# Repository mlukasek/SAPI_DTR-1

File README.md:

# SAPI-1 DTR-1 (Deska Testeru a RAM)

DTR-1 je modení deska pro starší 8-bitový počítač SAPI-1. Jedná se o poměrně univerzální desku, která může sloužit pro různé funkce podle nainstalovaného firmware. V současnosti firmware umožňuje:
- rychle (cca 2 min) nahrát obsah RAM disku ZRMD-1 z nebo do PC přes USB (za chodu SAPI i bez dalších desek ve sběrnici)
- nahradit desku DMR-1, resp. na ní obsažených DSM-1 a RAM-1Z (handshaking není zatím implementován)
- otestovat video RAM v AND-1Z/89
- otestovat základní RAM počítače

Deska DTR-1 využívá levný Cypress (Infineon) kit CY8CKIT-059 pro různé funkce. Základem kitu je PSoC (Programmable System on a Chip) CY8C5888LTI-LP097, který kromě procesor ARM Cortex-M3 obsahuje i propojovatelnou digitální a analogovou část (něco jako CPLD). Z kitu je potřeba odpájet některé součástky, které jinak zamezují funkci některých vývodů, jakožto standardních GPIO pinů a v podstatě tak kit funguje jen jako breakout z SMD na THT technologii, aby nebylo nutné pájet SMD pouzdro.

[Schéma zapojení](https://github.com/mlukasek/SAPI_DTR-1/blob/main/HW/DTR-1_v2021-05-06_SCH.pdf)

[Seznam součástek](https://github.com/mlukasek/SAPI_DTR-1/blob/main/HW/DTR-1_v2021-05-06_BOM.csv)

[Gerber/Excellon pro výrobu DPS](https://github.com/mlukasek/SAPI_DTR-1/blob/main/HW/Gerber/DTR-1_v2021-05-06_Gerber_cor.zip)

## Odpájení některých součástek z CY8CKIT-059

Pro správnou funkci DTR-1 je potřeba z desky CY8CKIT-059 odstranit (odpájet) některé součástky. Kit je částečně analogový a na některých pinech jsou součástky, převážně kondenzátory, které by nám digitální komunikaci na sběrnici kazili, proto je potřeba asi 6 kondíků a jeden odpor z desky odpájet. Já to dělám tak, že na součástku přidám cín tak, abych byl schopen hrotem páječky z boku ohřát oba konce současně a pak součástku snadno oddělám a přebytečný cín odsaji lankem.

Konkrétně se jedná o následující součástky:
- C7, C9, C12, C13 - SAR bypass capacitors
- C41, C42 - 32 kHz crystal capacitors
- R5 nebo C4 - CMOD
- R18 - User LED resistor
- SW1 - User push button (možno ponechat, ale nesmí se stisknout, jinak připojí A2 natvrdo na GND)

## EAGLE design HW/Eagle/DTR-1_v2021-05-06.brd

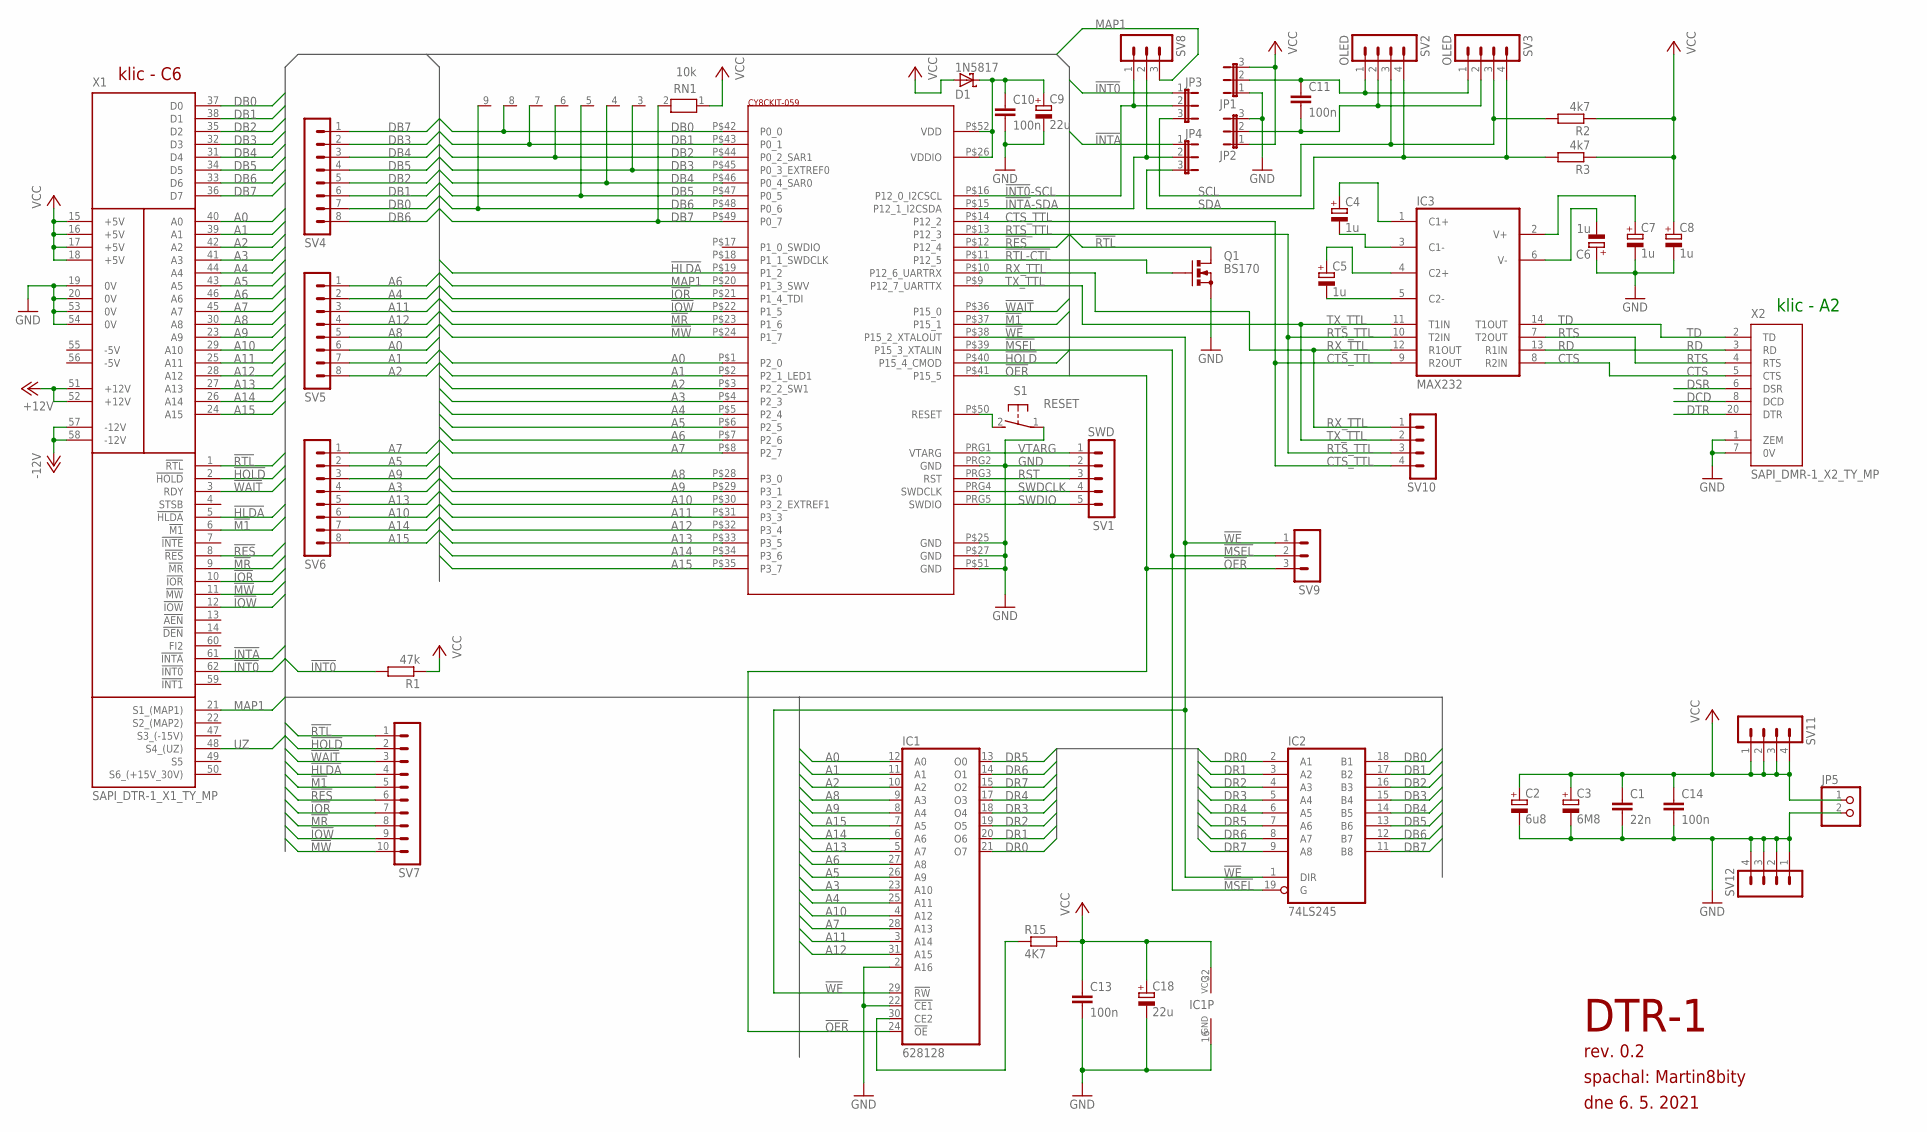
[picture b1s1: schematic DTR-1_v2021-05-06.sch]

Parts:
C1: 22n; C025-024X044
C2: 6u8; E5-4
C3: 6M8; E2,5-5
C4, C5, C6, C7, C8: 1u; E2,5-5
C9, C18: 22u; E2,5-5
C10, C13, C14: 100n; C025-024X044
C11: 100n; C050-025X075
D1: 1N5817; DO41-7.6
IC1: 628128; DIL32
IC2: 74LS245; DIL20
IC3: MAX232; DIL16
JP1, JP2, JP3, JP4: JP2E; JP2
JP5: PINHD-1X2; 1X02
Q1: BS170; SOT54E
R1: 47k; 0207/10
R2, R3: 4k7; 0207/10
R15: 4K7; 0207/10
RN1: 10k; RN-9
S1: RESET; B3F-31XX
SV1: SWD; MA05-1
SV2, SV3: OLED; MA04-1
SV4, SV5, SV6: MA08-1
SV7: MA10-1
SV8, SV9: MA03-1
SV10, SV11, SV12: MA04-1
U$1: CY8CKIT-059; PSOC-KIT-26
X1: SAPI_DTR-1_X1_TY_MP; TY5176211/DTR-1_X1
X2: SAPI_DMR-1_X2_TY_MP; TY5133011/DMR-1_X2

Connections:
!HLDA: SV7.4, U$1.P$19 (P1_2), X1.5 (!HLDA)
!HOLD: SV7.2, U$1.P$40 (P15_4_CMOD), X1.2 (!HOLD)
!INT0: JP3.1, R1.2, X1.62 (!INT0)
!INT0!-SCL: JP3.2, SV8.1, U$1.P$16 (P12_0_I2CSCL)
!INTA: JP4.1, X1.61 (!INTA)
!INTA!-SDA: JP4.2, SV8.2, U$1.P$15 (P12_1_I2CSDA)
!IOR: SV7.7, U$1.P$21 (P1_4_TDI), X1.10 (!IOR)
!IOW: SV7.9, U$1.P$22 (P1_5), X1.12 (!IOW)
!M1: SV7.5, U$1.P$37 (P15_1), X1.6 (!M1)
!MR: SV7.8, U$1.P$23 (P1_6), X1.9 (!MR)
!MSEL: IC2.19 (G), SV9.2, U$1.P$39 (P15_3_XTALIN)
!MW: SV7.10, U$1.P$24 (P1_7), X1.11 (!MW)
!OER: IC1.24 (!OE), SV9.3, U$1.P$41 (P15_5)
!RES: SV7.6, U$1.P$12 (P12_4), X1.8 (!RES)
!RTL: Q1.D, SV7.1, X1.1 (!RTL)
!RTL-CTL: Q1.G, U$1.P$11 (P12_5)
!WAIT: SV7.3, U$1.P$36 (P15_0), X1.3 (RDY)
!WE: IC1.29 (!RW), IC2.1 (DIR), SV9.1, U$1.P$38 (P15_2_XTALOUT)
+12V: X1.51 (+12V), X1.52 (+12V)
-12V: X1.57 (-12V), X1.58 (-12V)
A0: IC1.12 (A0), SV5.6, U$1.P$1 (P2_0), X1.40 (A0)
A1: IC1.11 (A1), SV5.7, U$1.P$2 (P2_1_LED1), X1.39 (A1)
A2: IC1.10 (A2), SV5.8, U$1.P$3 (P2_2_SW1), X1.42 (A2)
A3: IC1.23 (A10), SV6.4, U$1.P$4 (P2_3), X1.41 (A3)
A4: IC1.25 (A11), SV5.2, U$1.P$5 (P2_4), X1.44 (A4)
A5: IC1.26 (A9), SV6.2, U$1.P$6 (P2_5), X1.43 (A5)
A6: IC1.27 (A8), SV5.1, U$1.P$7 (P2_6), X1.46 (A6)
A7: IC1.28 (A13), SV6.1, U$1.P$8 (P2_7), X1.45 (A7)
A8: IC1.9 (A3), SV5.5, U$1.P$28 (P3_0), X1.30 (A8)
A9: IC1.8 (A4), SV6.3, U$1.P$29 (P3_1), X1.23 (A9)
A10: IC1.4 (A12), SV6.6, U$1.P$30 (P3_2_EXTREF1), X1.29 (A10)
A11: IC1.3 (A14), SV5.3, U$1.P$31 (P3_3), X1.25 (A11)
A12: IC1.31 (A15), SV5.4, U$1.P$32 (P3_4), X1.28 (A12)
A13: IC1.5 (A7), SV6.5, U$1.P$33 (P3_5), X1.27 (A13)
A14: IC1.6 (A6), SV6.7, U$1.P$34 (P3_6), X1.26 (A14)
A15: IC1.7 (A5), SV6.8, U$1.P$35 (P3_7), X1.24 (A15)
CTS: IC3.8 (R2IN), X2.5 (CTS)
CTS_TTL: IC3.9 (R2OUT), SV10.4, U$1.P$14 (P12_2)
DB0: IC2.18 (B1), RN1.8, SV4.7, U$1.P$42 (P0_0), X1.37 (D0)
DB1: IC2.17 (B2), RN1.7, SV4.6, U$1.P$43 (P0_1), X1.38 (D1)
DB2: IC2.16 (B3), RN1.6, SV4.5, U$1.P$44 (P0_2_SAR1), X1.35 (D2)
DB3: IC2.15 (B4), RN1.3, SV4.2, U$1.P$45 (P0_3_EXTREF0), X1.32 (D3)
DB4: IC2.14 (B5), RN1.4, SV4.3, U$1.P$46 (P0_4_SAR0), X1.31 (D4)
DB5: IC2.13 (B6), RN1.5, SV4.4, U$1.P$47 (P0_5), X1.34 (D5)
DB6: IC2.12 (B7), RN1.9, SV4.8, U$1.P$48 (P0_6), X1.33 (D6)
DB7: IC2.11 (B8), RN1.2, SV4.1, U$1.P$49 (P0_7), X1.36 (D7)
DCD: X2.8 (DCD)
DR0: IC1.21 (O7), IC2.2 (A1)
DR1: IC1.20 (O6), IC2.3 (A2)
DR2: IC1.19 (O5), IC2.4 (A3)
DR3: IC1.18 (O4), IC2.5 (A4)
DR4: IC1.17 (O3), IC2.6 (A5)
DR5: IC1.13 (O0), IC2.7 (A6)
DR6: IC1.14 (O1), IC2.8 (A7)
DR7: IC1.15 (O2), IC2.9 (A8)
DSR: X2.6 (DSR)
DTR: X2.20 (DTR)
GND: C1.2, C2.-, C3.-, C6.+, C7.-, C8.-, C9.-, C10.2, C13.2, C14.2, C18.-, IC1.2 (A16), IC1.16 (GND), IC1.22 (!CE1), IC2.10 (GND), IC3.15 (GND), JP1.1, JP2.3, JP5.2, Q1.S, S1.1, SV1.2, SV12.1, SV12.2, SV12.3, SV12.4, U$1.P$25 (GND), U$1.P$27 (GND), U$1.P$51 (GND), U$1.PRG2 (GND), X1.19 (0V), X1.20 (0V), X1.53 (0V), X1.54 (0V), X2.1 (ZEM), X2.7 (0V)
MAP1: SV8.3, U$1.P$20 (P1_3_SWV), X1.21 (S1_(MAP1))
unnamed: C9.+, C10.1, D1.C, U$1.P$26 (VDDIO), U$1.P$52 (VDD)
unnamed: S1.2 (S), U$1.P$50 (RESET)
unnamed: C11.1, JP1.2, SV2.1, SV3.1
unnamed: C6.-, IC3.6 (V-)
unnamed: C7.+, IC3.2 (V+)
unnamed: C5.-, IC3.5 (C2-)
unnamed: C5.+, IC3.4 (C2+)
unnamed: C4.-, IC3.3 (C1-)
unnamed: C4.+, IC3.1 (C1+)
unnamed: C11.2, JP2.2, SV2.2, SV3.2
unnamed: IC1.30 (CE2), R15.1
RD: IC3.13 (R1IN), X2.3 (RD)
RST: SV1.3, U$1.PRG3 (RST)
RTS: IC3.7 (T2OUT), X2.4 (RTS)
RTS_TTL: IC3.10 (T2IN), SV10.3, U$1.P$13 (P12_3)
RX_TTL: IC3.12 (R1OUT), SV10.1, U$1.P$10 (P12_6_UARTRX)
SCL: JP3.3, R2.2, SV2.3, SV3.3
SDA: JP4.3, R3.2, SV2.4, SV3.4
SWDCLK: SV1.4, U$1.PRG4 (SWDCLK)
SWDIO: SV1.5, U$1.PRG5 (SWDIO)
TD: IC3.14 (T1OUT), X2.2 (TD)
TX_TTL: IC3.11 (T1IN), SV10.2, U$1.P$9 (P12_7_UARTTX)
UZ: X1.48 (S4_(UZ))
VCC: C1.1, C2.+, C3.+, C8.+, C13.1, C14.1, C18.+, D1.A, IC1.32 (VCC), IC2.20 (VCC), IC3.16 (VCC), JP1.3, JP2.1, JP5.1, R1.1, R2.1, R3.1, R15.2, RN1.1, SV11.1, SV11.2, SV11.3, SV11.4, X1.15 (+5V), X1.16 (+5V), X1.17 (+5V), X1.18 (+5V)
VTARG: SV1.1, U$1.PRG1 (VTARG)

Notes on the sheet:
DTR-1
spachal: Martin8bity
dne 6. 5. 2021
klic - C6
klic - A2
rev. 0.2

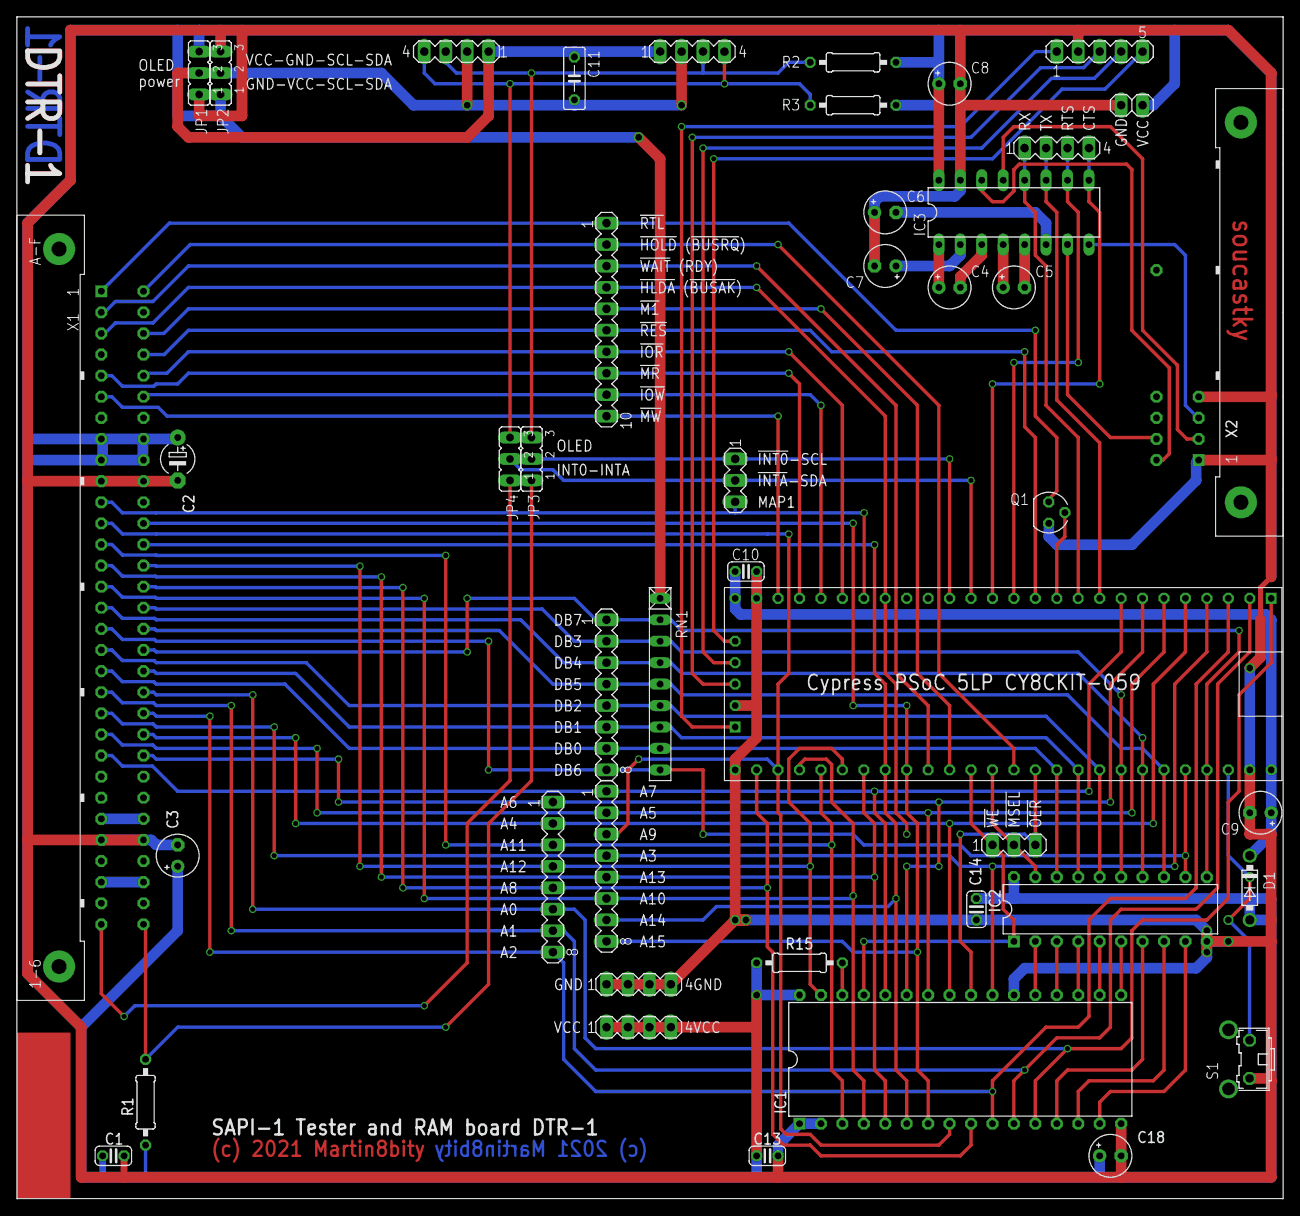
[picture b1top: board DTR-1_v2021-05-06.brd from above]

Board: 2 copper layers, 150.0 x 140.0 mm, 45 parts (0 on the bottom side), 80 nets.

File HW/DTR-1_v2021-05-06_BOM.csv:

SAPI-1 DTR-1 board partlist (BOM);;;;;
;;;;;
Qty;Parts;Value;Device;Package;Description
1;IC1;SRAM 628128/628512;TC551001CP;DIL32;MEMORY SRAM
1;IC2;74LS245;74LS245N;DIL20;Octal BUS TRANSCEIVER, 3-state
1;IC3;MAX232;MAX232;DIL16;RS232 TRANSCEIVER
1;Q1;BS170;BS170;SOT54E;N-CHANNEL MOS FET
1;D1;1N5817;1N5817-B;DO41-7.6;1.0A SCHOTTKY BARRIER RECTIFIER
1;R1;47k;R-EU_0207/10;0207/10;RESISTOR, European symbol
1;R15;4k7;R-EU_0207/10;0207/10;RESISTOR, European symbol
2;R2, R3;4k7;R-EU_0207/10;0207/10;RESISTOR, European symbol
1;RN1;DNI (optional data pull-up ~10k);RN08;RN-9;RESISTOR NETWORK
1;C1;22 nF;C-EU025-024X044;C025-024X044;CAPACITOR, European symbol
3;C10, C13, C14;100 nF;C-EU025-024X044;C025-024X044;CAPACITOR, European symbol
1;C11;100 nF;C-EU050-025X075;C050-025X075;CAPACITOR, European symbol
1;C2;6.8 uF;CPOL-EUE5-4;E5-4;POLARIZED CAPACITOR, European symbol
1;C3;6.8 uF;CPOL-EUE2.5-5;E2,5-5;POLARIZED CAPACITOR, European symbol
5;C4, C5, C6, C7, C8;1 uF;CPOL-EUE2.5-5;E2,5-5;POLARIZED CAPACITOR, European symbol
2;C9, C18;22 uF;CPOL-EUE2.5-5;E2,5-5;POLARIZED CAPACITOR, European symbol
2;JP1, JP2;OLED power select jumper;1x3 pin header;JP2;JUMPER
2;JP3, JP4;INT/OLED jumper;1x3 pin header;JP2;JUMPER
1;JP5;optional serial module power;1x2 pin header;1X02;PIN HEADER
1;S1;RESET;31-XX;B3F-31XX;OMRON SWITCH
1;SV1;SWD;1x5 female header + 1x5 pin header;MA05-1;PIN HEADER
1;SV10;optional serial module IO;1x4 pin header;MA04-1;PIN HEADER
2;SV11, SV12;optional logic analyser connector;1x4 pin header;MA04-1;PIN HEADER
2;SV2, SV3;OLED;MA04-1;MA04-1;PIN HEADER
3;SV4, SV5, SV6;optional logic analyser connector;1x8 pin header;MA08-1;PIN HEADER
1;SV7;optional logic analyser connector;1x10 pin header;MA10-1;PIN HEADER
2;SV8, SV9;optional logic analyser connector;1x3 pin header;MA03-1;PIN HEADER
1;U$1;CY8CKIT-059;CY8CKIT-059;;
2;U$1;CY8CKIT-059 I/O pins;1x28 female header + 1x28 pin header;;
1;U$1;CY8CKIT-059 SWD pins;1x5 female header + 1x5 pin header;;
1;X1;SAPI bus;SAPI_DTR-1_X1_TY_MP;TY5176211;
1;X2;RS-232c;SAPI_DMR-1_X2_TY_MP;TY5133011;

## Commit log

2021-06-14 BOM update
2021-06-14 images added
2021-06-20 Cypress PSoC Creator sources added.
2023-09-19 Reset signal corrected for BS170 usage, sources update to PSoC Creator 4.4

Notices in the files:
HW/Eagle/DTR-1_v2021-05-06.brd:
(c) 2021 Martin8bity
